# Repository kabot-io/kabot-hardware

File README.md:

# Kabot Hardware

Kabot is an open-source, compact educational mobile robot. This repository contains its mechanical, electronic, and hardware production files.

## Project status

The hardware prototype is complete.

## FOSS toolchain

The hardware was designed entirely with free and open-source software (FOSS):

- [FreeCAD 1.1.1](https://www.freecad.org/) for the mechanical design
- [KiCad 10.0.4](https://www.kicad.org/) for the electronic design

Using these versions is recommended for the best compatibility with the source files.

## BOM

The mechanical parts are designed using [FreeCAD](https://www.freecad.org/) and 3D printed with some little exceptions, which were not viable to print due to the low cost of China-sourced parts, that is (amount for 10 robots):

- [Wheels](https://www.aliexpress.com/item/1005006221405033.html) - 20pcs
- [Torx self-tapping screws](https://www.aliexpress.com/item/1005011545930370.html) - 100pcs
- [N20 Gearmotors with 7CPR encoders](https://www.aliexpress.com/item/1005007102441781.html) - 20pcs
- [ToF distance sensor](https://www.aliexpress.com/item/1005008119148487.html) - 10pcs
- [Motor to PCB cables](https://www.aliexpress.com/item/1005007277030322.html) - 20pcs

## Electronics

The electronics has been designed using [KiCad](https://www.kicad.org/) and consist of few distinct sections (however, on a single PCB).

### Processing section  
Based on the [ESP32-S3-N16R8 MCU on Wroom-1 module](https://documentation.espressif.com/esp32-s3-wroom-1_wroom-1u_datasheet_en.pdf), which is responsible for communication with the PC, fetching data from the sensors, and executing control messages - driving the motors.

This MCU has a [built-in USB JTAG](https://docs.espressif.com/projects/esp-idf/en/stable/esp32s3/api-guides/jtag-debugging/index.html) interface, which allows for flashing and debugging the robot firmware without the need of *any* external tools, besides USB-C cable. 

There is also onboard USB HUB ([CH334F](https://cdn-learn.adafruit.com/assets/assets/000/131/435/original/CH334DS1.PDF?1721660148)) and USB-to-serial adapter ([CH343P](https://cdn-learn.adafruit.com/assets/assets/000/134/549/original/CH343DS1.PDF?1737477957)), which allows for connecting to the robot over the raw UART interface, which exposes [first-stage bootloader](https://docs.espressif.com/projects/esp-idf/en/stable/esp32s3/api-guides/bootloader.html) logs, and a connector which allows for splitting the USB-C lanes, and injecting offboard processing units, such as embedded Linux board (instead of the beefy PC, to make the robot self-contained if needed) 

### Power section  
The USB-C connector that is used to program the robot, is also used to charge the robot built-in battery, which is a single Lithium-Ion 18650 sized cell. The same chip is also responsible for stepping the battery voltage up to 5V, which is then fed to the motor drivers to have somehat stable motor power supply, and stabilized to 3.3V for the MCU. The chip is the thing used in powerbanks - [INJOINIC IP5306](https://www.lcsc.com/datasheet/C181692.pdf).

Motors are driven by two [DRV8837](https://www.ti.com/lit/ds/symlink/drv8838.pdf) motor drivers (up to 1.8A per motor). Each motor driver is supplied via [INA219](https://www.ti.com/lit/ds/symlink/ina219.pdf) I2C Current/Power monitor. The motors are chinese [N20 sized 298:1 micro gearmotors, equipped with magnetic incremental encoders](https://pl.aliexpress.com/item/1005007102441781.html). The power supply branch for the rest of the system also has it's own IN219 sensor. There is also voltage divider connected directly do the battery terminals (or rather semi-directly - via a switch that gets opened when the robot is not powered up, to avoid entirely draining the battery). 

### Sensors section  

Besides the current sensors and encoders, robot has a bunch of on-board sensors:
- 6 Degrees of Freedon Inertial Measurement Unit: [TDK ICM-42670-L](https://datasheet.lcsc.com/datasheet/pdf/874d19cb3cf7cf4a72e58391bfc479df.pdf)
- 3 Degrees of Freedom Magnetometer: [MEMSIC MMC5603NJ](https://www.lcsc.com/datasheet/C404328.pdf)
- dual visible light sensors (left and right): [LITEON LTR-303-ALS](https://www.lcsc.com/datasheet/C364577.pdf)
- distance sensor - [ST VL53L0X](https://www.st.com/resource/en/datasheet/vl53l0x.pdf) on the GY-530 footprint module - this allows for supplying different distance sensors, sucha as 8x8 grid [ST VL53L5X](https://www.st.com/resource/en/datasheet/vl53l5cx.pdf) ToF sensor

These allow for implementing a wide variety of algorithms - from simple [BEAM](https://en.wikipedia.org/wiki/BEAM_robotics)-like photovores, trough IMU sensor fusion up to localization and mapping.

The board also supplies a bunch of addresable RGB LEDs.

## Repository structure

| Directory | Contents |
| --- | --- |
| [`freecad/`](freecad/) | FreeCAD mechanical source files for the chassis, battery holder, motor mounts, wheels, and related parts. |
| [`kicad/`](kicad/) | KiCad schematics, PCB layout, symbols, footprints, and supporting EDA files. |
| [`production/`](production/) | Files used to manufacture the PCB and print the chassis, including Gerber and drill files, a bill of materials (BOM), and pick-and-place data. |

## License

Copyright 2026 Krzysztof Pochwała.

The hardware design files are available under the [Creative Commons Attribution-NonCommercial-ShareAlike 4.0 International license](LICENSE.md) (CC BY-NC-SA 4.0). You may share and adapt the files with attribution, for non-commercial purposes, provided adaptations are distributed under the same license.

## More information

Visit [kabot.io](https://kabot.io/).

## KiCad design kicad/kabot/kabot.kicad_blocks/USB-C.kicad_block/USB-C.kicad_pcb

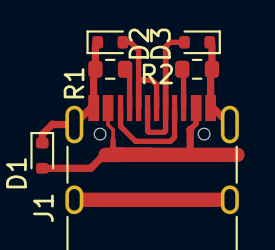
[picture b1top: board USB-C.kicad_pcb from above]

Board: 2 copper layers, 6 parts (0 on the bottom side), 7 nets.

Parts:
D1, D2, D3: LESD5D5; D_SOD-523
J1: USB_C_Receptacle_USB2.0; USB_C_Receptacle_HRO_TYPE-C-31-M-12
R1, R2: 5k1; R_0603_1608Metric

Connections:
+5VD: D1.2 (A2), J1.A4 (VBUS), J1.A9 (VBUS), J1.B4 (VBUS), J1.B9 (VBUS)
/USB_D+: D3.2 (A2), J1.A6 (D+), J1.B6 (D+)
/USB_D-: D2.2 (A2), J1.A7 (D-), J1.B7 (D-)
GND: D1.1 (A1), D2.1 (A1), D3.1 (A1), J1.A1 (GND), J1.A12 (GND), J1.B1 (GND), J1.B12 (GND), J1.S1 (SHIELD), R1.2, R2.2
unnamed: J1.A5 (CC1), R1.1
unnamed: J1.B5 (CC2), R2.1
unnamed: J1.A8 (SBU1), J1.B8 (SBU2)

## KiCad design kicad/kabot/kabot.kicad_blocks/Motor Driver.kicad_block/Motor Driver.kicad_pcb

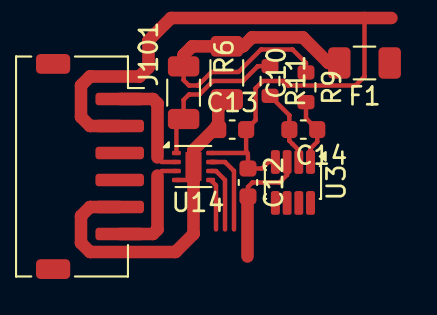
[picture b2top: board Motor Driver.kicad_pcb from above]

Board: 2 copper layers, 11 parts (0 on the bottom side), 8 nets.

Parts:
C10: 22u; C_1206_3216Metric
C12, C13, C14: 100n; C_0603_1608Metric
F1: 1.8A; Fuse_1206_3216Metric
J101: Conn_01x06_MountingPin; JST_ZH_S6B-ZR-SM4A-TF_1x06-1MP_P1.50mm_Horizontal
R6: 0R1; R_1206_3216Metric
R9, R11: 1R; R_0603_1608Metric
U3: INA219AxDCN; SOT-23-8
U14: DRV8837; WSON-8-1EP_2x2mm_P0.5mm_EP0.9x1.6mm

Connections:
/Motor Driver/3V3: C12.1, C13.1, J101.2, U3.4 (VS), U14.8 (VCC)
/Motor Driver/GND: C10.2, C12.2, C13.2, J101.5, U3.3 (GND), U14.4 (GND), U14.9 (GND)
unnamed: C10.1, F1.2, R6.1, R9.1
unnamed: J101.1, U14.2 (OUT1)
unnamed: J101.6, U14.3 (OUT2)
unnamed: C14.1, R9.2, U3.1 (IN+)
unnamed: C14.2, R11.2, U3.2 (IN-)
unnamed: R6.2, R11.1, U14.1 (VM)

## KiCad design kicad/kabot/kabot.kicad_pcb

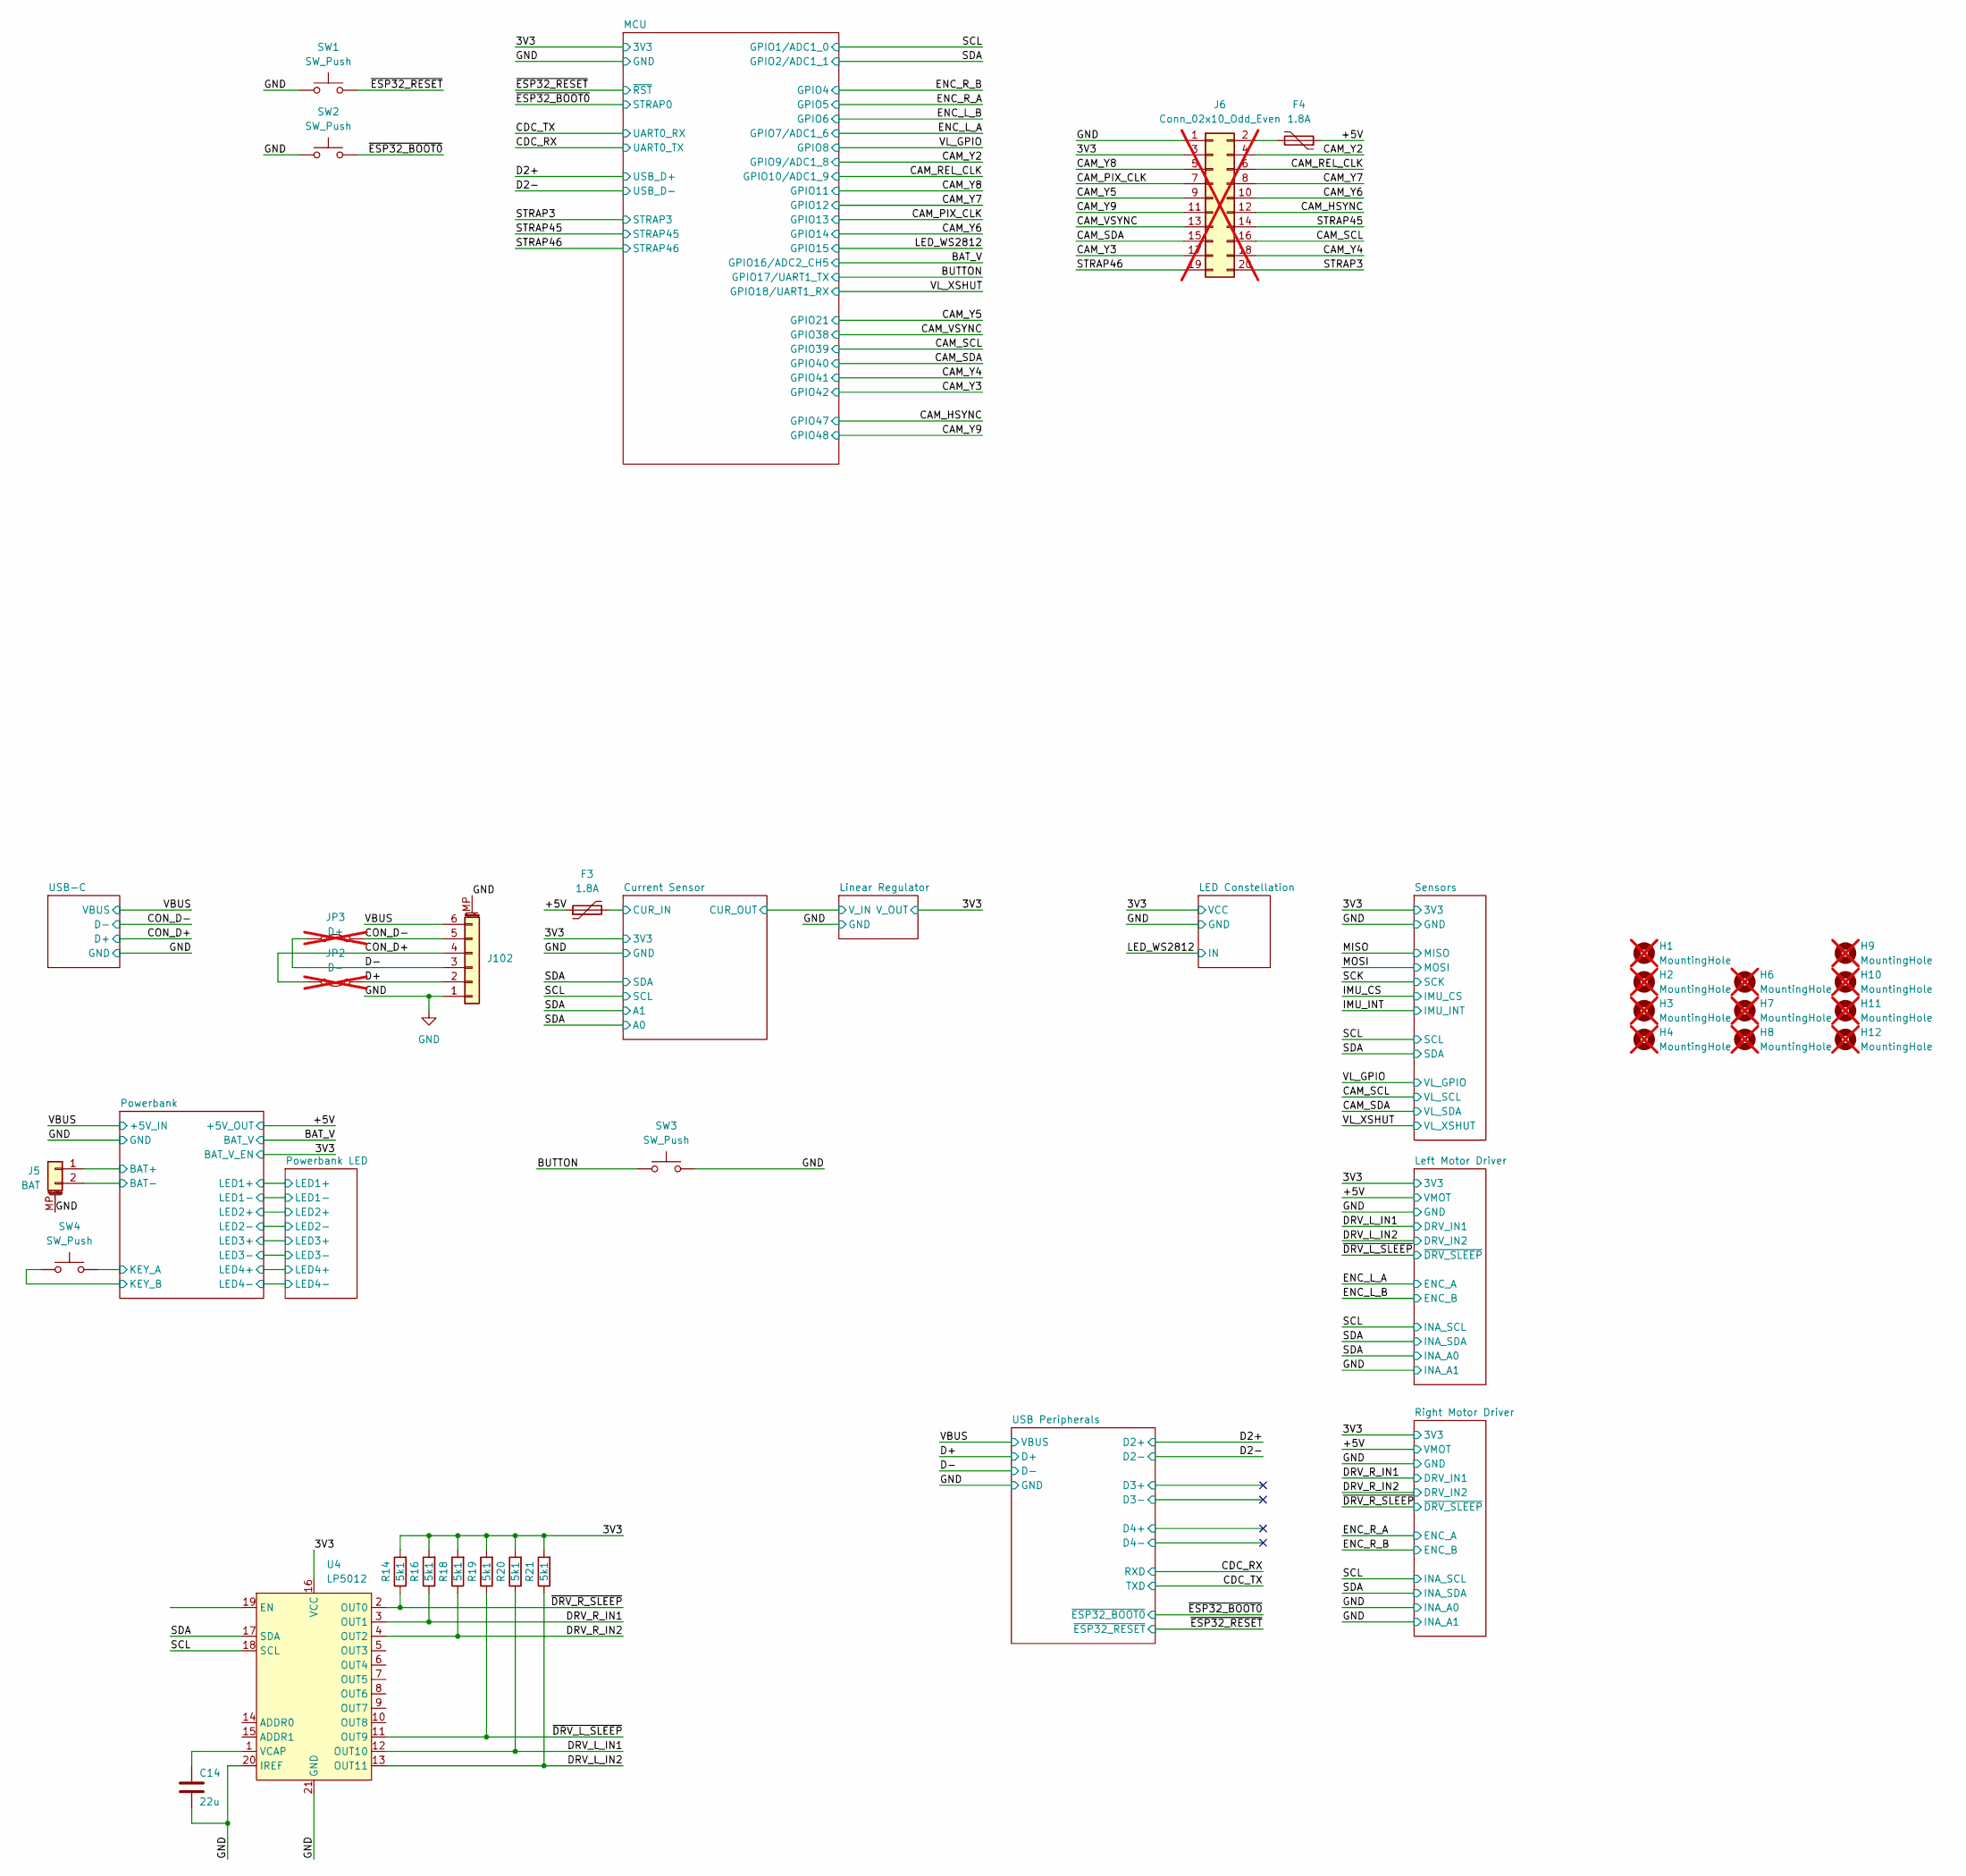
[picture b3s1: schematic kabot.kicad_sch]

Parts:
C14: 22u; C_1206_3216Metric; JLC C12891
F3, F4: 1.8A; Fuse_1206_3216Metric; JLC C5375706
H1, H2, H3, H4, H6, H7, H8, H9, H10, H11, H12: MountingHole; MountingHole_3.5mm; not fitted
J5: BAT; JST_ZH_S2B-ZR-SM4A-TF_1x02-1MP_P1.50mm_Horizontal
J6: Conn_02x10_Odd_Even; PinSocket_2x10_P2.54mm_Vertical; not fitted
J102: Conn_01x06_MountingPin; JST_ZH_S6B-ZR-SM4A-TF_1x06-1MP_P1.50mm_Horizontal
JP2: D-; SolderJumper-2_P1.3mm_Bridged_RoundedPad1.0x1.5mm; not fitted
JP3: D+; SolderJumper-2_P1.3mm_Bridged_RoundedPad1.0x1.5mm; not fitted
R14, R16, R18, R19, R20, R21: 5k1; R_0603_1608Metric; JLC C23186
SW1, SW2, SW3, SW4: SW_Push; SW_Push_SPST_NO_Alps_SKRK
U4: LP5012; WQFN-20-1EP_3x3mm_P0.4mm_EP1.7x1.7mm; JLC C1849481

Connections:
/3V3: J6.3, R14.2, R16.2, R18.2, R19.2, R20.2, R21.2, U4.16 (VCC); also elsewhere on the board
/+5V: F3.1, F4.1; also elsewhere on the board
/BUTTON: SW3.1; also elsewhere on the board
/CAM_HSYNC: J6.12; also elsewhere on the board
/CAM_PIX_CLK: J6.7; also elsewhere on the board
/CAM_REL_CLK: J6.6; also elsewhere on the board
/CAM_SCL: J6.16; also elsewhere on the board
/CAM_SDA: J6.15; also elsewhere on the board
/CAM_VSYNC: J6.13; also elsewhere on the board
/CAM_Y2: J6.4; also elsewhere on the board
/CAM_Y3: J6.17; also elsewhere on the board
/CAM_Y4: J6.18; also elsewhere on the board
/CAM_Y5: J6.9; also elsewhere on the board
/CAM_Y6: J6.10; also elsewhere on the board
/CAM_Y7: J6.8; also elsewhere on the board
/CAM_Y8: J6.5; also elsewhere on the board
/CAM_Y9: J6.11; also elsewhere on the board
/CON_D+: J102.4, JP2.2 (B); also elsewhere on the board
/CON_D-: J102.5, JP3.1 (A); also elsewhere on the board
/Current Sensor/CUR_IN: F3.2; also elsewhere on the board
/D+: J102.2, JP2.1 (A); also elsewhere on the board
/D-: J102.3, JP3.2 (B); also elsewhere on the board
/DRV_L_IN1: R20.1, U4.12 (OUT10); also elsewhere on the board
/DRV_L_IN2: R21.1, U4.13 (OUT11); also elsewhere on the board
/DRV_R_IN1: R16.1, U4.3 (OUT1); also elsewhere on the board
/DRV_R_IN2: R18.1, U4.4 (OUT2); also elsewhere on the board
/Powerbank/BAT+: J5.1; also elsewhere on the board
/Powerbank/KEY_A: SW4.2; also elsewhere on the board
/SCL: U4.18 (SCL); also elsewhere on the board
/SDA: U4.17 (SDA); also elsewhere on the board
/STRAP3: J6.20; also elsewhere on the board
/STRAP45: J6.14; also elsewhere on the board
/STRAP46: J6.19; also elsewhere on the board
/VBUS: J102.6; also elsewhere on the board
/~DRV_L_SLEEP: R19.1, U4.11 (OUT9); also elsewhere on the board
/~DRV_R_SLEEP: R14.1, U4.2 (OUT0); also elsewhere on the board
/~ESP32_BOOT0: SW2.1; also elsewhere on the board
/~ESP32_RESET: SW1.2; also elsewhere on the board
GND: C14.2, J5.2, J5.MP (MountPin), J6.1, J102.1, J102.MP (MountPin), SW1.1, SW2.2, SW3.2, SW4.1, U4.20 (IREF), U4.21 (GND); also elsewhere on the board
unnamed: F4.2, J6.2
unnamed: C14.1, U4.1 (VCAP)

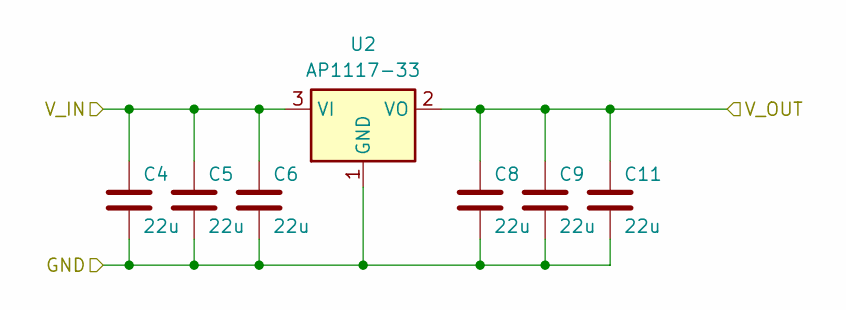
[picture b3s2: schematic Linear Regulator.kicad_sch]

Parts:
C4, C5, C6, C8, C9, C11: 22u; C_1206_3216Metric; JLC C12891
U2: AP1117-33; SOT-223-3_TabPin2; JLC C6186

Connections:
/3V3: C8.1, C9.1, C11.1, U2.2 (VO); also elsewhere on the board
/Current Sensor/CUR_OUT: C4.1, C5.1, C6.1, U2.3 (VI); also elsewhere on the board
GND: C4.2, C5.2, C6.2, C8.2, C9.2, C11.2, U2.1 (GND); also elsewhere on the board

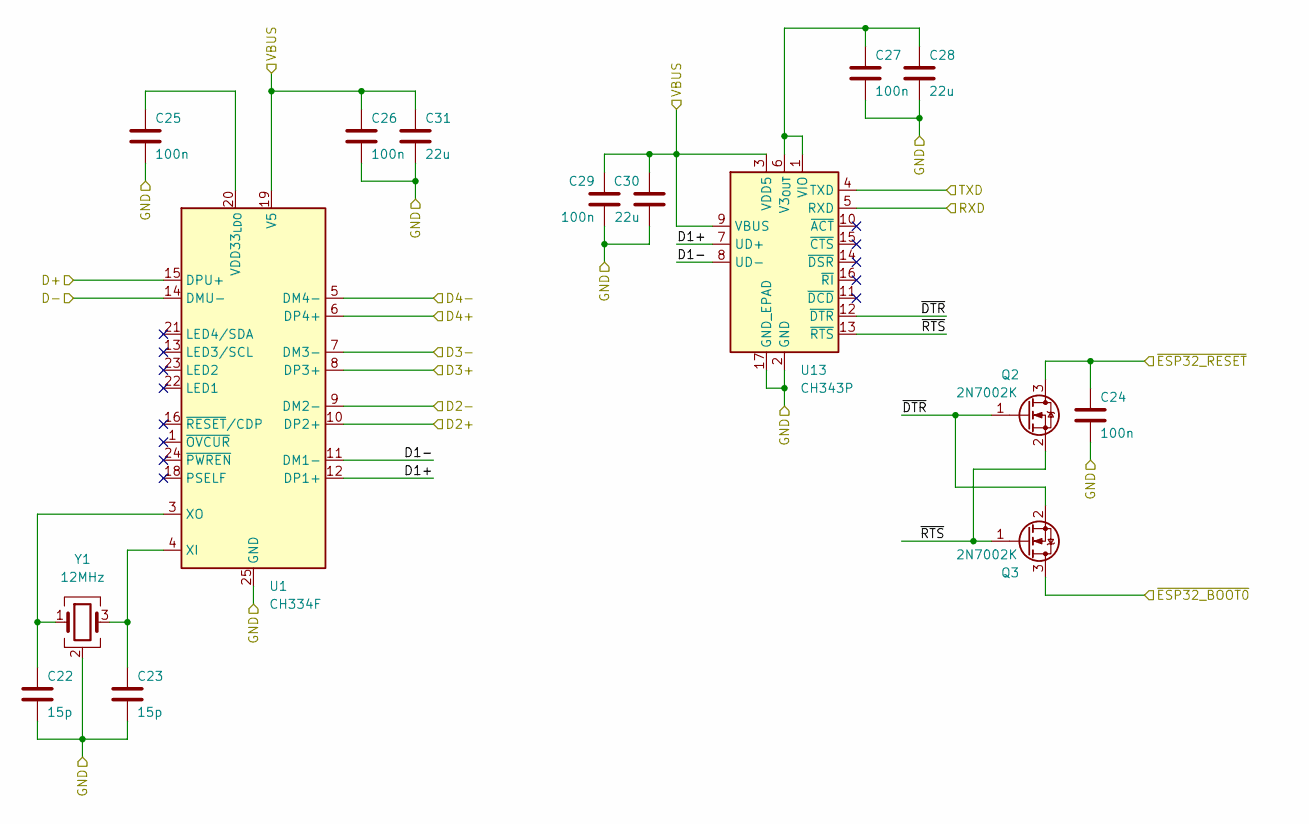
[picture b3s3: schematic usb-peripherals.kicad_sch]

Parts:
C22, C23: 15p; C_0603_1608Metric; JLC C1644
C24, C25, C26, C27, C29: 100n; C_0603_1608Metric; JLC C14663
C28, C30, C31: 22u; C_1206_3216Metric; JLC C12891
Q2, Q3: 2N7002K; SOT-23; JLC C8545
U1: CH334F; QFN-24-1EP_4x4mm_P0.5mm_EP2.7x2.7mm; JLC C5187527
U13: CH343P; WCH_QFN-16-1EP_3x3mm_P0.5mm_EP1.8x1.8mm
Y1: 12MHz; Crystal_SMD_3225-4Pin_3.2x2.5mm; JLC C9002

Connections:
/CDC_RX: U13.5 (RXD); also elsewhere on the board
/CDC_TX: U13.4 (TXD); also elsewhere on the board
/D2+: U1.10 (DP2+); also elsewhere on the board
/D2-: U1.9 (DM2-); also elsewhere on the board
/D+: U1.15 (DPU+); also elsewhere on the board
/D-: U1.14 (DMU-); also elsewhere on the board
/USB Peripherals/D1+: U1.12 (DP1+), U13.7 (UD+)
/USB Peripherals/D1-: U1.11 (DM1-), U13.8 (UD-)
/USB Peripherals/D3+: U1.8 (DP3+)
/USB Peripherals/D3-: U1.7 (DM3-)
/USB Peripherals/D4+: U1.6 (DP4+)
/USB Peripherals/D4-: U1.5 (DM4-)
/USB Peripherals/~DTR: Q2.1 (G), Q3.2 (S), U13.12 (~DTR)
/USB Peripherals/~RTS: Q2.2 (S), Q3.1 (G), U13.13 (~RTS)
/VBUS: C26.1, C29.1, C30.1, C31.1, U1.19 (V5), U13.3 (VDD5), U13.9 (VBUS); also elsewhere on the board
/~ESP32_BOOT0: Q3.3 (D); also elsewhere on the board
/~ESP32_RESET: C24.1, Q2.3 (D); also elsewhere on the board
GND: C22.2, C23.2, C24.2, C25.2, C26.2, C27.2, C28.2, C29.2, C30.2, C31.2, U1.25 (GND), U13.2 (GND), U13.17 (GND_EPAD), Y1.2 (G), Y1.4 (G); also elsewhere on the board
unnamed: C25.1, U1.20 (VDD33_{LDO})
unnamed: C23.1, U1.4 (XI), Y1.3
unnamed: C22.1, U1.3 (XO), Y1.1
unnamed: C27.1, C28.1, U13.1 (VIO), U13.6 (V3_{OUT})

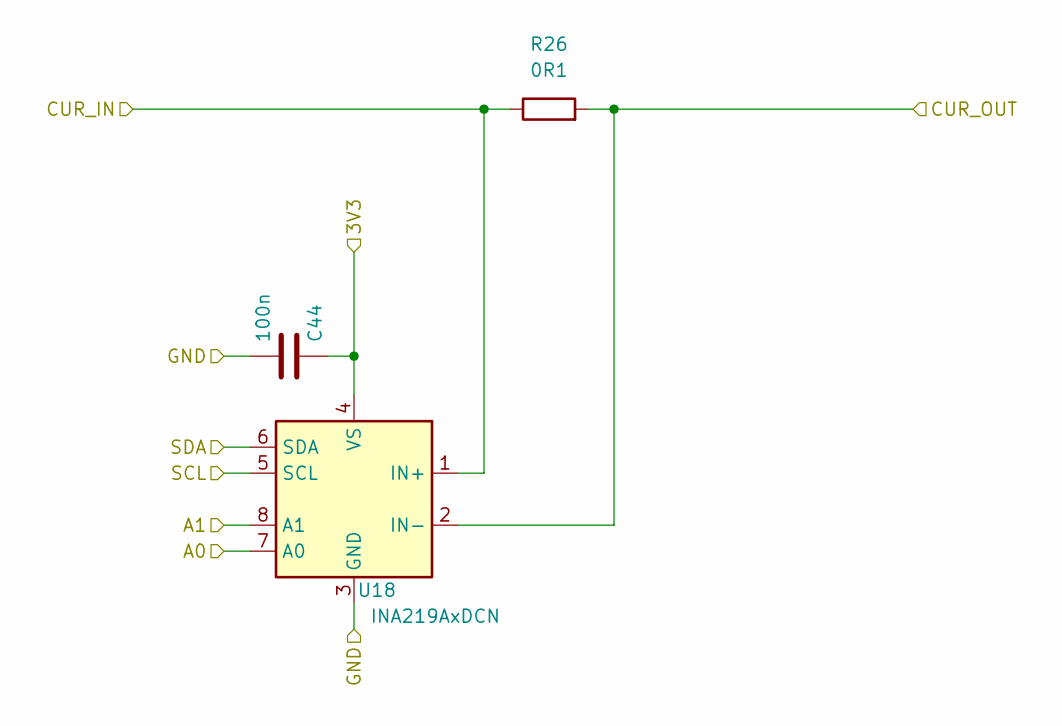
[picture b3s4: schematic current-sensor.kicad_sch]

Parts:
C44: 100n; C_0603_1608Metric; JLC C14663
R26: 0R1; R_1206_3216Metric; JLC C25334
U18: INA219AxDCN; SOT-23-8

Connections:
/3V3: C44.1, U18.4 (VS); also elsewhere on the board
/Current Sensor/CUR_IN: R26.1, U18.1 (IN+); also elsewhere on the board
/Current Sensor/CUR_OUT: R26.2, U18.2 (IN-); also elsewhere on the board
/SCL: U18.5 (SCL); also elsewhere on the board
/SDA: U18.6 (SDA), U18.7 (A0), U18.8 (A1); also elsewhere on the board
GND: C44.2, U18.3 (GND); also elsewhere on the board

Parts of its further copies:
C38, C42: 100n; C_0603_1608Metric; JLC C14663
R17, R23: 0R1; R_1206_3216Metric; JLC C25334
U9, U17: INA219AxDCN; SOT-23-8

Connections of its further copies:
/3V3: C38.1, C42.1, U9.4 (VS), U17.4 (VS); also elsewhere on the board
/Left Motor Driver/Current Sensor/CUR_IN: R23.1, U17.1 (IN+); also elsewhere on the board
/Left Motor Driver/Current Sensor/CUR_OUT: R23.2, U17.2 (IN-); also elsewhere on the board
/Right Motor Driver/Current Sensor/CUR_IN: R17.1, U9.1 (IN+); also elsewhere on the board
/Right Motor Driver/Current Sensor/CUR_OUT: R17.2, U9.2 (IN-); also elsewhere on the board
/SCL: U9.5 (SCL), U17.5 (SCL); also elsewhere on the board
/SDA: U9.6 (SDA), U17.6 (SDA), U17.7 (A0); also elsewhere on the board
GND: C38.2, C42.2, U9.3 (GND), U9.7 (A0), U9.8 (A1), U17.3 (GND), U17.8 (A1); also elsewhere on the board

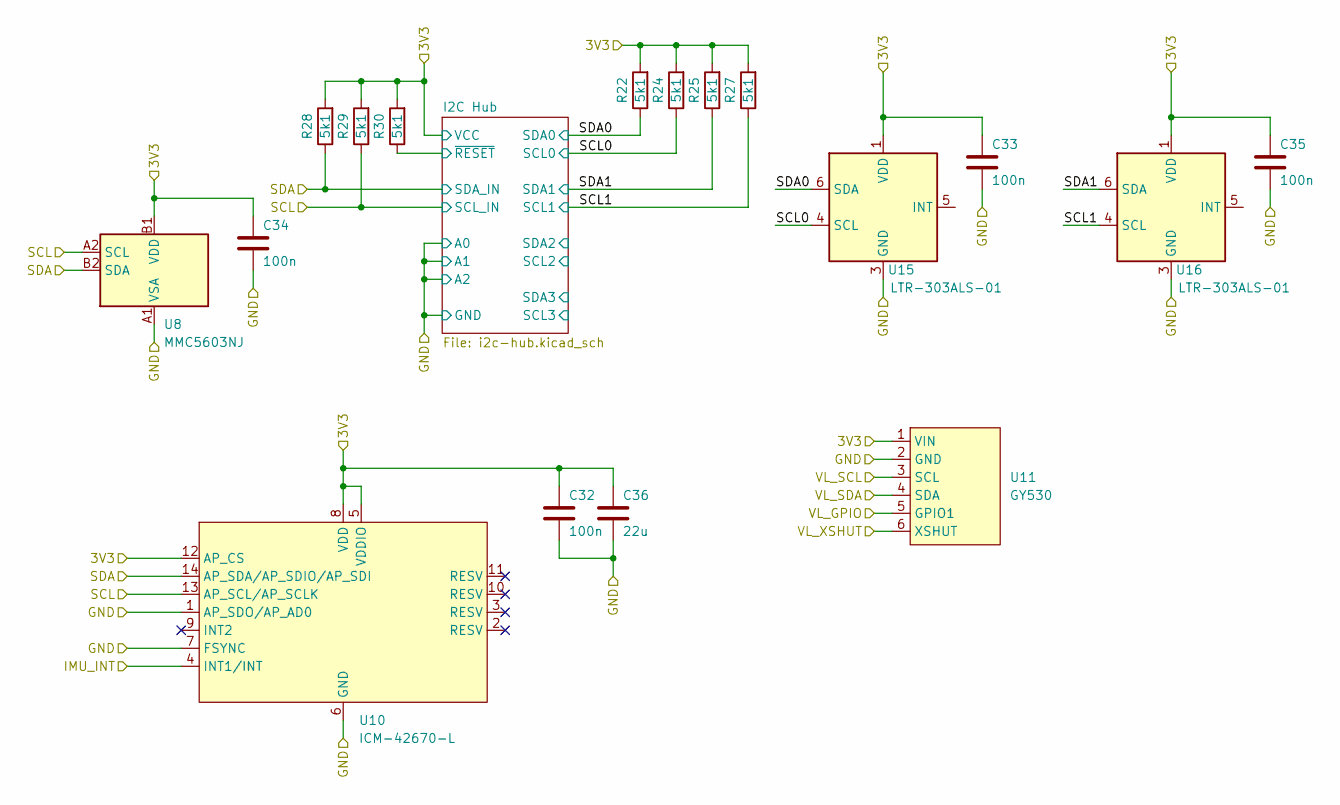
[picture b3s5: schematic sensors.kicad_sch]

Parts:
C32, C33, C34, C35: 100n; C_0603_1608Metric; JLC C14663
C36: 22u; C_1206_3216Metric; JLC C12891
R22, R24, R25, R27, R28, R29, R30: 5k1; R_0603_1608Metric; JLC C23186
U8: MMC5603NJ; WLP-4_0.86x0.86mm_P0.4mm; JLC C404328
U10: ICM-42670-L; LGA-14_3x2.5mm_P0.5mm_LayoutBorder3x4y; JLC C49073546
U11: GY530
U15, U16: LTR-303ALS-01; Lite-On_LTR-303ALS-01; JLC C364577

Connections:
/3V3: C32.1, C33.1, C34.1, C35.1, C36.1, R22.2, R24.2, R25.2, R27.2, R28.2, R29.2, R30.2, U8.B1 (VDD), U10.5 (VDDIO), U10.8 (VDD), U10.12 (AP_CS), U11.1 (VIN), U15.1 (VDD), U16.1 (VDD); also elsewhere on the board
/CAM_SCL: U11.3 (SCL); also elsewhere on the board
/CAM_SDA: U11.4 (SDA); also elsewhere on the board
/IMU_INT: U10.4 (INT1/INT)
/SCL: R29.1, U8.A2 (SCL), U10.13 (AP_SCL/AP_SCLK); also elsewhere on the board
/SDA: R28.1, U8.B2 (SDA), U10.14 (AP_SDA/AP_SDIO/AP_SDI); also elsewhere on the board
/Sensors/I2C Hub/~RESET: R30.1; also elsewhere on the board
/Sensors/SCL0: R24.1, U15.4 (SCL); also elsewhere on the board
/Sensors/SCL1: R27.1, U16.4 (SCL); also elsewhere on the board
/Sensors/SDA0: R22.1, U15.6 (SDA); also elsewhere on the board
/Sensors/SDA1: R25.1, U16.6 (SDA); also elsewhere on the board
/VL_GPIO: U11.5 (GPIO1); also elsewhere on the board
/VL_XSHUT: U11.6 (XSHUT); also elsewhere on the board
GND: C32.2, C33.2, C34.2, C35.2, C36.2, U8.A1 (VSA), U10.1 (AP_SDO/AP_AD0), U10.6 (GND), U10.7 (FSYNC), U11.2 (GND), U15.3 (GND), U16.3 (GND); also elsewhere on the board

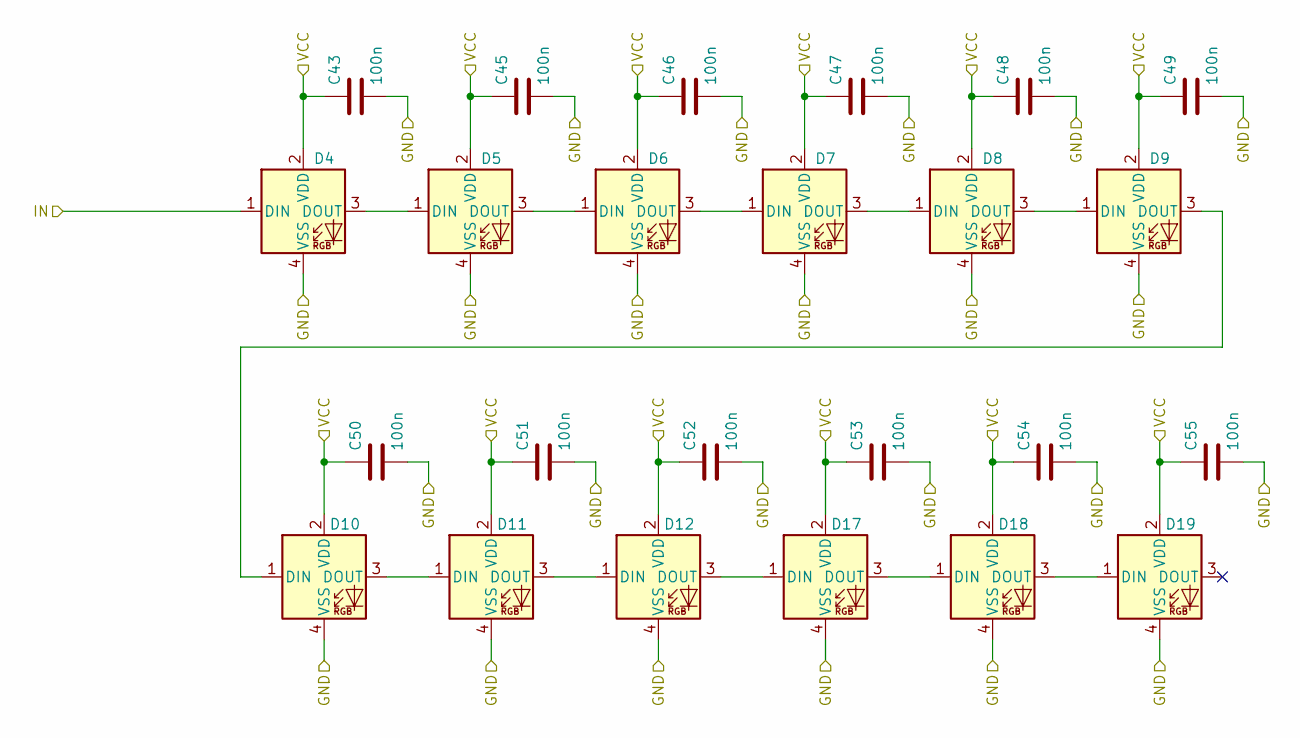
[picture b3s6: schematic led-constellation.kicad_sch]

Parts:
C43, C45, C46, C47, C48, C49, C50, C51, C52, C53, C54, C55: 100n; C_0603_1608Metric; JLC C14663
D4, D5, D6, D7, D8, D9, D10, D11, D12, D17, D18, D19: XL2121RGBC-WS2812B; LED_ASMB-KTF0-0A306; JLC C5349957

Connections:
/3V3: C43.1, C45.1, C46.1, C47.1, C48.1, C49.1, C50.1, C51.1, C52.1, C53.1, C54.1, C55.1, D4.2 (VDD), D5.2 (VDD), D6.2 (VDD), D7.2 (VDD), D8.2 (VDD), D9.2 (VDD), D10.2 (VDD), D11.2 (VDD), D12.2 (VDD), D17.2 (VDD), D18.2 (VDD), D19.2 (VDD); also elsewhere on the board
/LED_WS2812: D4.1 (DIN); also elsewhere on the board
GND: C43.2, C45.2, C46.2, C47.2, C48.2, C49.2, C50.2, C51.2, C52.2, C53.2, C54.2, C55.2, D4.4 (VSS), D5.4 (VSS), D6.4 (VSS), D7.4 (VSS), D8.4 (VSS), D9.4 (VSS), D10.4 (VSS), D11.4 (VSS), D12.4 (VSS), D17.4 (VSS), D18.4 (VSS), D19.4 (VSS); also elsewhere on the board
unnamed: D4.3 (DOUT), D5.1 (DIN)
unnamed: D5.3 (DOUT), D6.1 (DIN)
unnamed: D6.3 (DOUT), D7.1 (DIN)
unnamed: D7.3 (DOUT), D8.1 (DIN)
unnamed: D8.3 (DOUT), D9.1 (DIN)
unnamed: D9.3 (DOUT), D10.1 (DIN)
unnamed: D10.3 (DOUT), D11.1 (DIN)
unnamed: D11.3 (DOUT), D12.1 (DIN)
unnamed: D12.3 (DOUT), D17.1 (DIN)
unnamed: D17.3 (DOUT), D18.1 (DIN)
unnamed: D18.3 (DOUT), D19.1 (DIN)

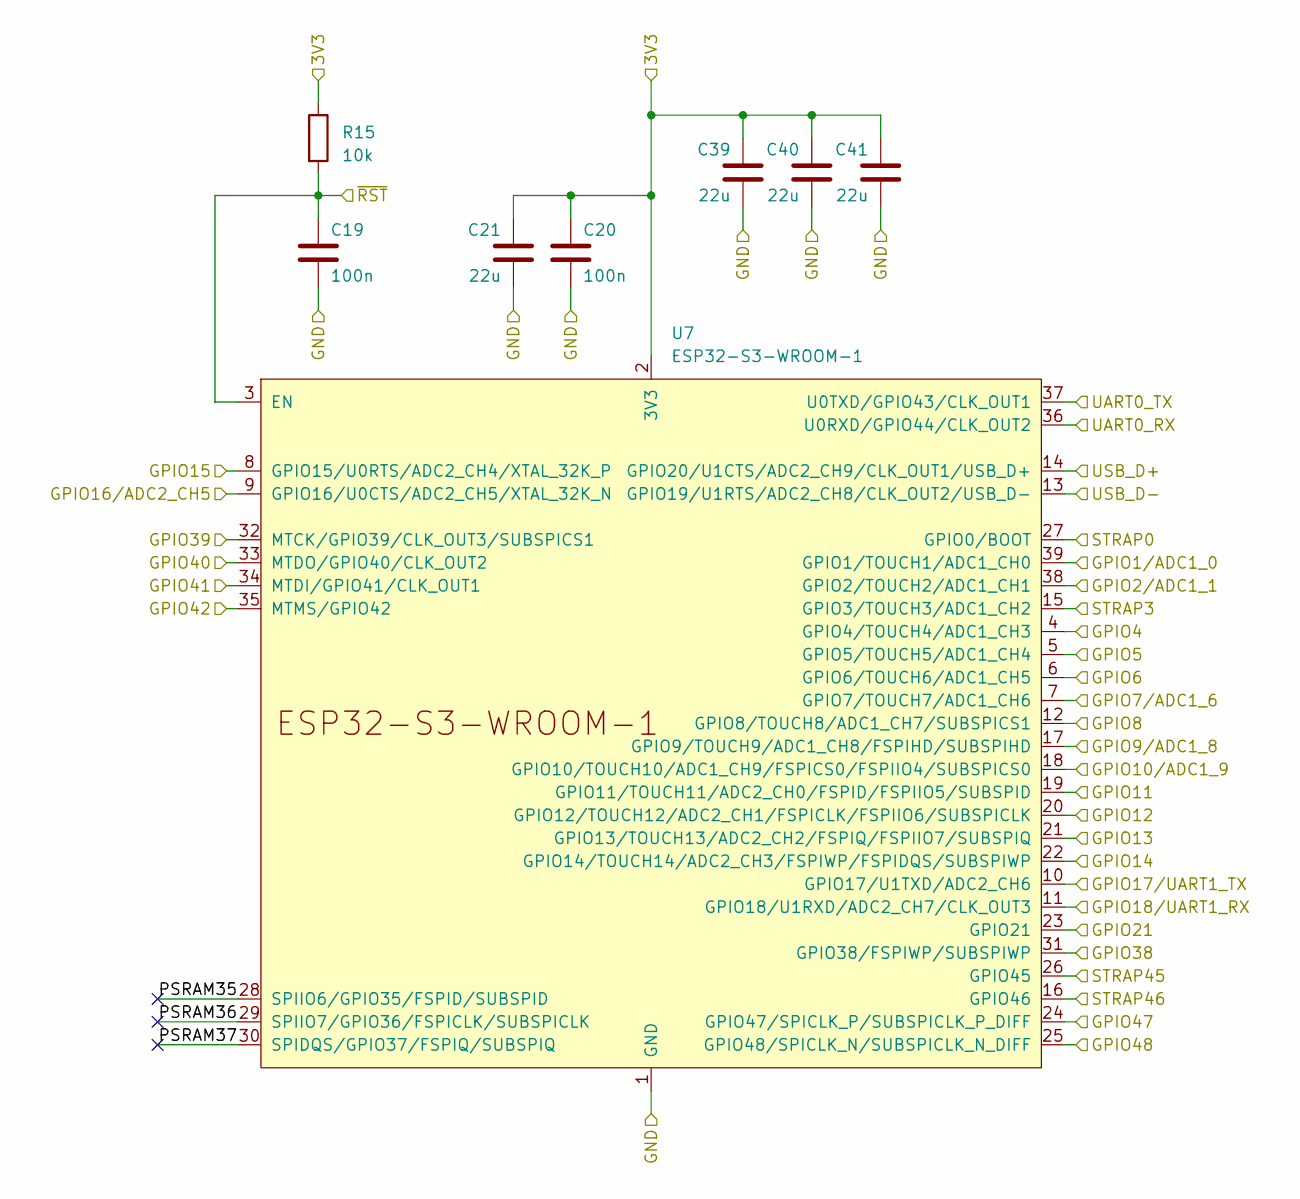
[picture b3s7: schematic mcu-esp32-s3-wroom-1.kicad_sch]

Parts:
C19, C20: 100n; C_0603_1608Metric; JLC C14663
C21, C39, C40, C41: 22u; C_1206_3216Metric; JLC C12891
R15: 10k; R_0603_1608Metric; JLC C25804
U7: ESP32-S3-WROOM-1

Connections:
/3V3: C20.1, C21.1, C39.1, C40.1, C41.1, R15.1, U7.2 (3V3); also elsewhere on the board
/BAT_V: U7.9 (GPIO16/U0CTS/ADC2_CH5/XTAL_32K_N); also elsewhere on the board
/BUTTON: U7.10 (GPIO17/U1TXD/ADC2_CH6); also elsewhere on the board
/CAM_HSYNC: U7.24 (GPIO47/SPICLK_P/SUBSPICLK_P_DIFF); also elsewhere on the board
/CAM_PIX_CLK: U7.21 (GPIO13/TOUCH13/ADC2_CH2/FSPIQ/FSPIIO7/S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); also elsewhere on the board
/CAM_REL_CLK: U7.18 (GPIO10/TOUCH10/ADC1_CH9/FSPICS0/FSPIIO4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); also elsewhere on the board
/CAM_SCL: U7.32 (MTCK/GPIO39/CLK_OUT3/SUBSPICS1); also elsewhere on the board
/CAM_SDA: U7.33 (MTDO/GPIO40/CLK_OUT2); also elsewhere on the board
/CAM_VSYNC: U7.31 (GPIO38/FSPIWP/SUBSPIWP); also elsewhere on the board
/CAM_Y2: U7.17 (GPIO9/TOUCH9/ADC1_CH8/FSPIHD/SUBSPIHD); also elsewhere on the board
/CAM_Y3: U7.35 (MTMS/GPIO42); also elsewhere on the board
/CAM_Y4: U7.34 (MTDI/GPIO41/CLK_OUT1); also elsewhere on the board
/CAM_Y5: U7.23 (GPIO21); also elsewhere on the board
/CAM_Y6: U7.22 (GPIO14/TOUCH14/ADC2_CH3/FSPIWP/FSPIDQS/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); also elsewhere on the board
/CAM_Y7: U7.20 (GPIO12/TOUCH12/ADC2_CH1/FSPICLK/FSPIIO6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); also elsewhere on the board
/CAM_Y8: U7.19 (GPIO11/TOUCH11/ADC2_CH0/FSPID/FSPIIO5/S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); also elsewhere on the board
/CAM_Y9: U7.25 (GPIO48/SPICLK_N/SUBSPICLK_N_DIFF); also elsewhere on the board
/CDC_RX: U7.37 (U0TXD/GPIO43/CLK_OUT1); also elsewhere on the board
/CDC_TX: U7.36 (U0RXD/GPIO44/CLK_OUT2); also elsewhere on the board
/D2+: U7.14 (GPIO20/U1CTS/ADC2_CH9/CLK_OUT1/USB_D+); also elsewhere on the board
/D2-: U7.13 (GPIO19/U1RTS/ADC2_CH8/CLK_OUT2/USB_D-); also elsewhere on the board
/ENC_L_A: U7.7 (GPIO7/TOUCH7/ADC1_CH6); also elsewhere on the board
/ENC_L_B: U7.6 (GPIO6/TOUCH6/ADC1_CH5); also elsewhere on the board
/ENC_R_A: U7.5 (GPIO5/TOUCH5/ADC1_CH4); also elsewhere on the board
/ENC_R_B: U7.4 (GPIO4/TOUCH4/ADC1_CH3); also elsewhere on the board
/LED_WS2812: U7.8 (GPIO15/U0RTS/ADC2_CH4/XTAL_32K_P); also elsewhere on the board
/MCU/PSRAM35: U7.28 (SPIIO6/GPIO35/FSPID/SUBSPID)
/MCU/PSRAM36: U7.29 (SPIIO7/GPIO36/FSPICLK/SUBSPICLK)
/MCU/PSRAM37: U7.30 (SPIDQS/GPIO37/FSPIQ/SUBSPIQ)
/SCL: U7.39 (GPIO1/TOUCH1/ADC1_CH0); also elsewhere on the board
/SDA: U7.38 (GPIO2/TOUCH2/ADC1_CH1); also elsewhere on the board
/STRAP3: U7.15 (GPIO3/TOUCH3/ADC1_CH2); also elsewhere on the board
/STRAP45: U7.26 (GPIO45); also elsewhere on the board
/STRAP46: U7.16 (GPIO46); also elsewhere on the board
/VL_GPIO: U7.12 (GPIO8/TOUCH8/ADC1_CH7/SUBSPICS1); also elsewhere on the board
/VL_XSHUT: U7.11 (GPIO18/U1RXD/ADC2_CH7/CLK_OUT3); also elsewhere on the board
/~ESP32_BOOT0: U7.27 (GPIO0/BOOT); also elsewhere on the board
/~ESP32_RESET: C19.1, R15.2, U7.3 (EN); also elsewhere on the board
GND: C19.2, C20.2, C21.2, C39.2, C40.2, C41.2, U7.1 (GND), U7.40 (GND), U7.41 (GND); also elsewhere on the board

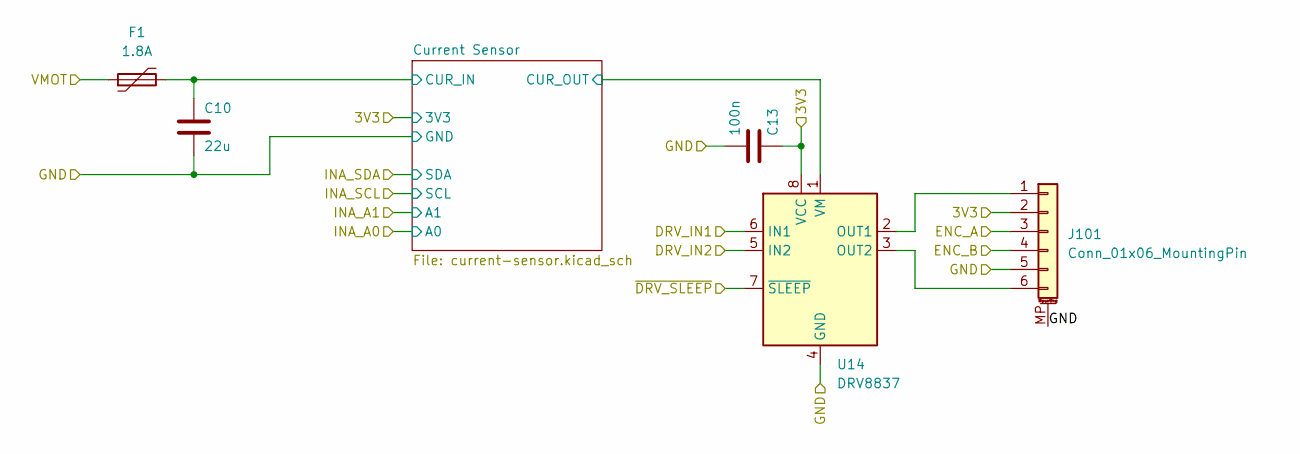
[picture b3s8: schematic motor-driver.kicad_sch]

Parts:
C10: 22u; C_1206_3216Metric; JLC C12891
C13: 100n; C_0603_1608Metric; JLC C14663
F1: 1.8A; Fuse_1206_3216Metric; JLC C5375706
J101: Conn_01x06_MountingPin; JST_ZH_S6B-ZR-SM4A-TF_1x06-1MP_P1.50mm_Horizontal
U14: DRV8837; WSON-8-1EP_2x2mm_P0.5mm_EP0.9x1.6mm; JLC C39159

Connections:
/3V3: C13.1, J101.2, U14.8 (VCC); also elsewhere on the board
/+5V: F1.1; also elsewhere on the board
/DRV_L_IN1: U14.6 (IN1); also elsewhere on the board
/DRV_L_IN2: U14.5 (IN2); also elsewhere on the board
/ENC_L_A: J101.3; also elsewhere on the board
/ENC_L_B: J101.4; also elsewhere on the board
/Left Motor Driver/Current Sensor/CUR_IN: C10.1, F1.2; also elsewhere on the board
/Left Motor Driver/Current Sensor/CUR_OUT: U14.1 (VM); also elsewhere on the board
/~DRV_L_SLEEP: U14.7 (~SLEEP); also elsewhere on the board
GND: C10.2, C13.2, J101.5, J101.MP (MountPin), U14.4 (GND), U14.9 (GND); also elsewhere on the board
unnamed: J101.1, U14.2 (OUT1)
unnamed: J101.6, U14.3 (OUT2)

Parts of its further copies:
C12: 22u; C_1206_3216Metric; JLC C12891
C18: 100n; C_0603_1608Metric; JLC C14663
F2: 1.8A; Fuse_1206_3216Metric; JLC C5375706
J1: Conn_01x06_MountingPin; JST_ZH_S6B-ZR-SM4A-TF_1x06-1MP_P1.50mm_Horizontal
U6: DRV8837; WSON-8-1EP_2x2mm_P0.5mm_EP0.9x1.6mm; JLC C39159

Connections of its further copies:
/3V3: C18.1, J1.2, U6.8 (VCC); also elsewhere on the board
/+5V: F2.1; also elsewhere on the board
/DRV_R_IN1: U6.6 (IN1); also elsewhere on the board
/DRV_R_IN2: U6.5 (IN2); also elsewhere on the board
/ENC_R_A: J1.3; also elsewhere on the board
/ENC_R_B: J1.4; also elsewhere on the board
/Right Motor Driver/Current Sensor/CUR_IN: C12.1, F2.2; also elsewhere on the board
/Right Motor Driver/Current Sensor/CUR_OUT: U6.1 (VM); also elsewhere on the board
/~DRV_R_SLEEP: U6.7 (~SLEEP); also elsewhere on the board
GND: C12.2, C18.2, J1.5, J1.MP (MountPin), U6.4 (GND), U6.9 (GND); also elsewhere on the board
unnamed: J1.1, U6.2 (OUT1)
unnamed: J1.6, U6.3 (OUT2)

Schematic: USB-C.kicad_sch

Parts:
D1, D2, D3: LESD5D5; D_SOD-523; JLC C383211
J8: USB_C_Receptacle_USB2.0_16P; USB_C_Receptacle_GCT_USB4105-xx-A_16P_TopMnt_Horizontal
R1, R2: 5k1; R_0603_1608Metric; JLC C23186

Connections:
/CON_D+: D3.2 (A2), J8.A6 (D+), J8.B6 (D+); also elsewhere on the board
/CON_D-: D2.2 (A2), J8.A7 (D-), J8.B7 (D-); also elsewhere on the board
/VBUS: D1.2 (A2), J8.A4 (VBUS), J8.A9 (VBUS), J8.B4 (VBUS), J8.B9 (VBUS); also elsewhere on the board
GND: D1.1 (A1), D2.1 (A1), D3.1 (A1), J8.A1 (GND), J8.A12 (GND), J8.B1 (GND), J8.B12 (GND), J8.SH (SHIELD), R1.2, R2.2; also elsewhere on the board
unnamed: J8.A5 (CC1), R1.1
unnamed: J8.B5 (CC2), R2.1
